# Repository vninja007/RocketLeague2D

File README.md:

# Rocket League 2D

Vrishak's attempt at a popular consumer game, replicated in 2D through microcontrollers and TFTs. This is a quarter 3 project for Robotics 2 finished in ~3 weeks.

This game relicates a very minimalistic version of turning, moving, ball collisions, friction, and wall collisions. Single player for now, will be multiplayer soon.

# Usage

Code is available at `code`. Working code (and essentially final code) is available at `code/working`.

This program is compiled and meant to be for NodeMCU-32S, a variant of the ESP32 board. Graphics are optimized through [TFT eSPI](https://github.com/Bodmer/TFT_eSPI). 

Code and all finished by approximately 2024-03-21, fancy documentation completed 2024-04-09.

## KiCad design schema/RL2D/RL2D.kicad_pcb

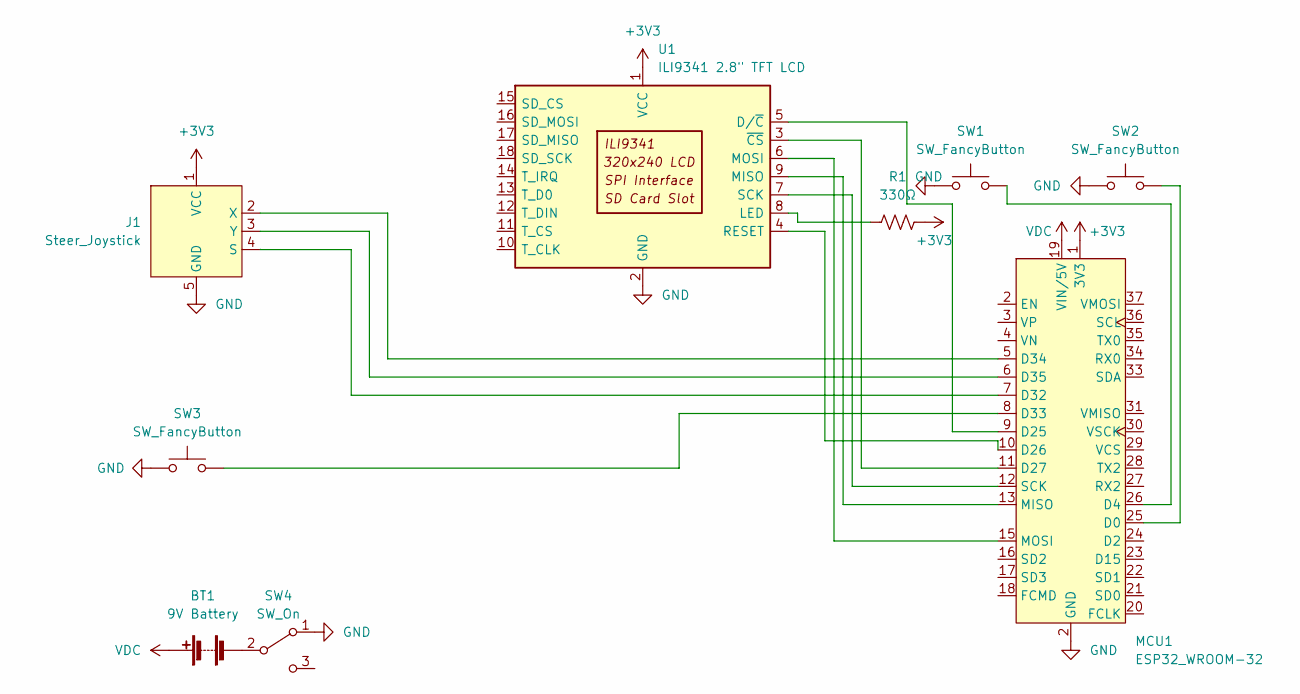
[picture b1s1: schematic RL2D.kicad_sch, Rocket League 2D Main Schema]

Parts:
BT1: 9V Battery; JST_XH_B2B-XH-A_1x02_P2.50mm_Vertical
J1: Steer_Joystick; Joystick
MCU1: ESP32_WROOM-32; ESP32
R1: 330Ω; R_Axial_DIN0207_L6.3mm_D2.5mm_P15.24mm_Horizontal
SW1, SW2, SW3: SW_FancyButton; FancyButton
SW4: SW_On; Switch
U1: ILI9341 2.8" TFT LCD; ILI9341 2.8inch

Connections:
+3V3: J1.1 (VCC), MCU1.1 (3V3), R1.2, U1.1 (VCC)
GND: J1.5 (GND), MCU1.2 (GND), SW1.1, SW2.1, SW3.1, SW4.1 (A), U1.2 (GND)
unnamed: BT1.2 (-), SW4.2 (B)
unnamed: J1.2 (X), MCU1.5 (D34)
unnamed: J1.3 (Y), MCU1.6 (D35)
unnamed: J1.4 (S), MCU1.7 (D32)
unnamed: MCU1.8 (D33), SW3.2
unnamed: MCU1.9 (D25), U1.5 (D/~C)
unnamed: MCU1.10 (D26), U1.4 (RESET)
unnamed: MCU1.11 (D27), U1.3 (~CS)
unnamed: MCU1.12 (SCK), U1.7 (SCK)
unnamed: MCU1.13 (MISO), U1.9 (MISO)
unnamed: MCU1.25 (D0), SW2.2
unnamed: MCU1.26 (D4), SW1.2
unnamed: MCU1.15 (MOSI), U1.6 (MOSI)
unnamed: R1.1, U1.8 (LED)
VDC: BT1.1 (+), MCU1.19 (VIN/5V)

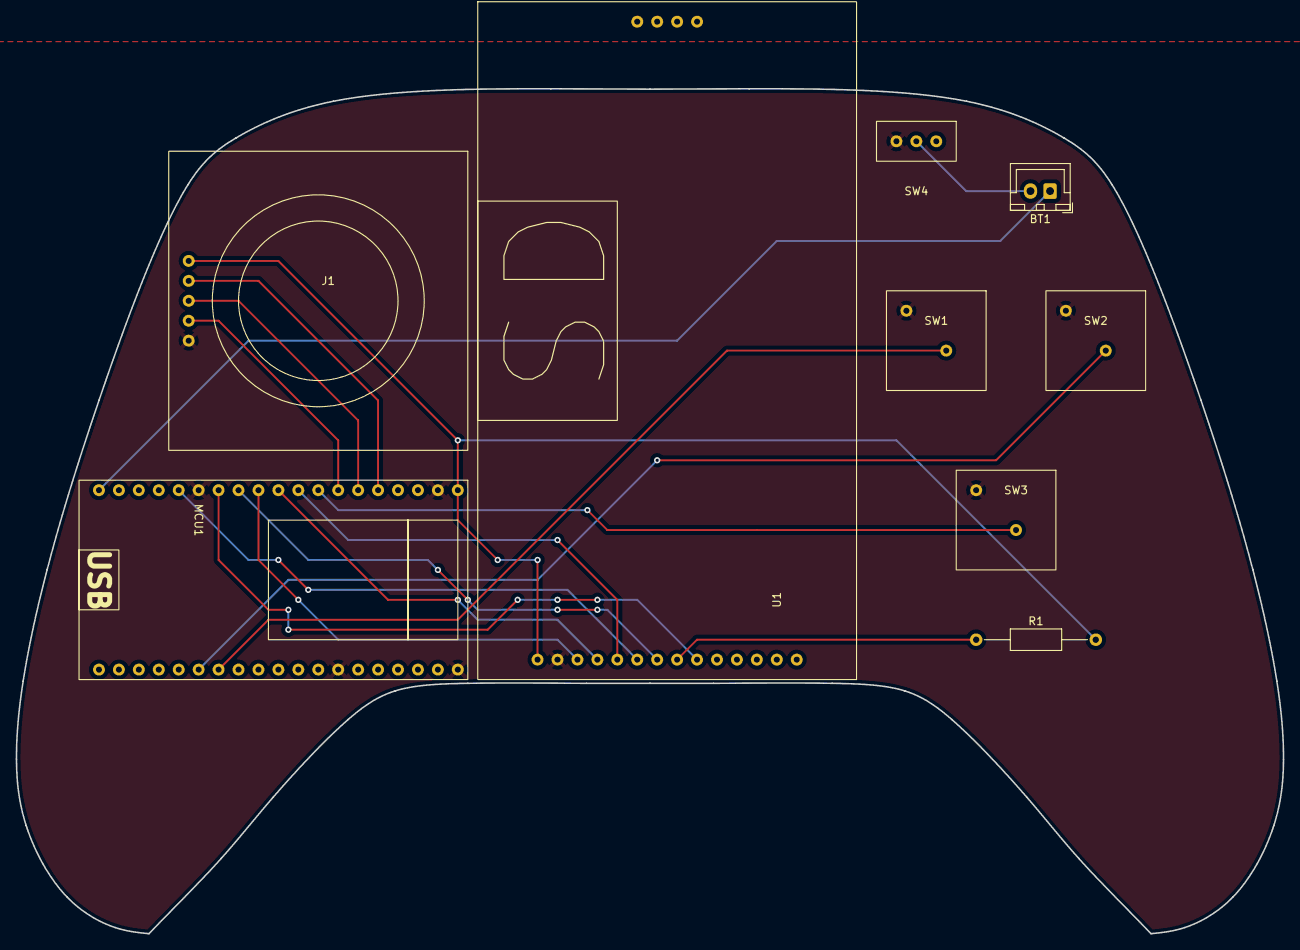
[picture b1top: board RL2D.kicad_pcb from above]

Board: 2 copper layers, 161.4 x 107.6 mm, 9 parts (0 on the bottom side), 17 nets.

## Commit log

2024-03-04 progress 3/4
2024-03-07 progress 3/7
2024-03-09 new esp32 schemas
2024-03-09 pcbout
2024-03-09 no backups
2024-03-09 really no backups
2024-03-11 newpcb
2024-03-14 progress 3/14
2024-03-19 dvd logo moving around
2024-03-19 functional collisions
2024-03-19 one player game
2024-03-19 basically single player
2024-03-19 singleplayer done
2024-04-09 This is not actually a redistribution, but rather just a implementation of the library so technically MIT license by adafruit is not required.
2024-04-09 Revert "singleplayer done"
    This reverts commit 57e053e3743347fbdcdcfb2a93f918bebcdca897.
2024-04-09 cleanup a lot
2024-04-09 dump
2024-04-09 morecleanup
